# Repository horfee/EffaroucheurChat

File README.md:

# Effaroucheur à Chat

This project is a design of a board, based on ESP32, to control ultra sound speaker according to infrared motion sensors.

It is powered by 2 solar panels, with a LDO MP2161GJ-Z to power efficiently the device.

Used components are :
- MP2161GJ-Z
- ESP32 WROOM
- TP4056 as battery charger
- HC-SR501 for motion sensors
- << insert speaker ref here >>
- FT232RL to discuss with ESP32 for flash phase
- UMH3N to enabled RTS/DTR mechanism

Flash firmware will come later.

Current design is this :

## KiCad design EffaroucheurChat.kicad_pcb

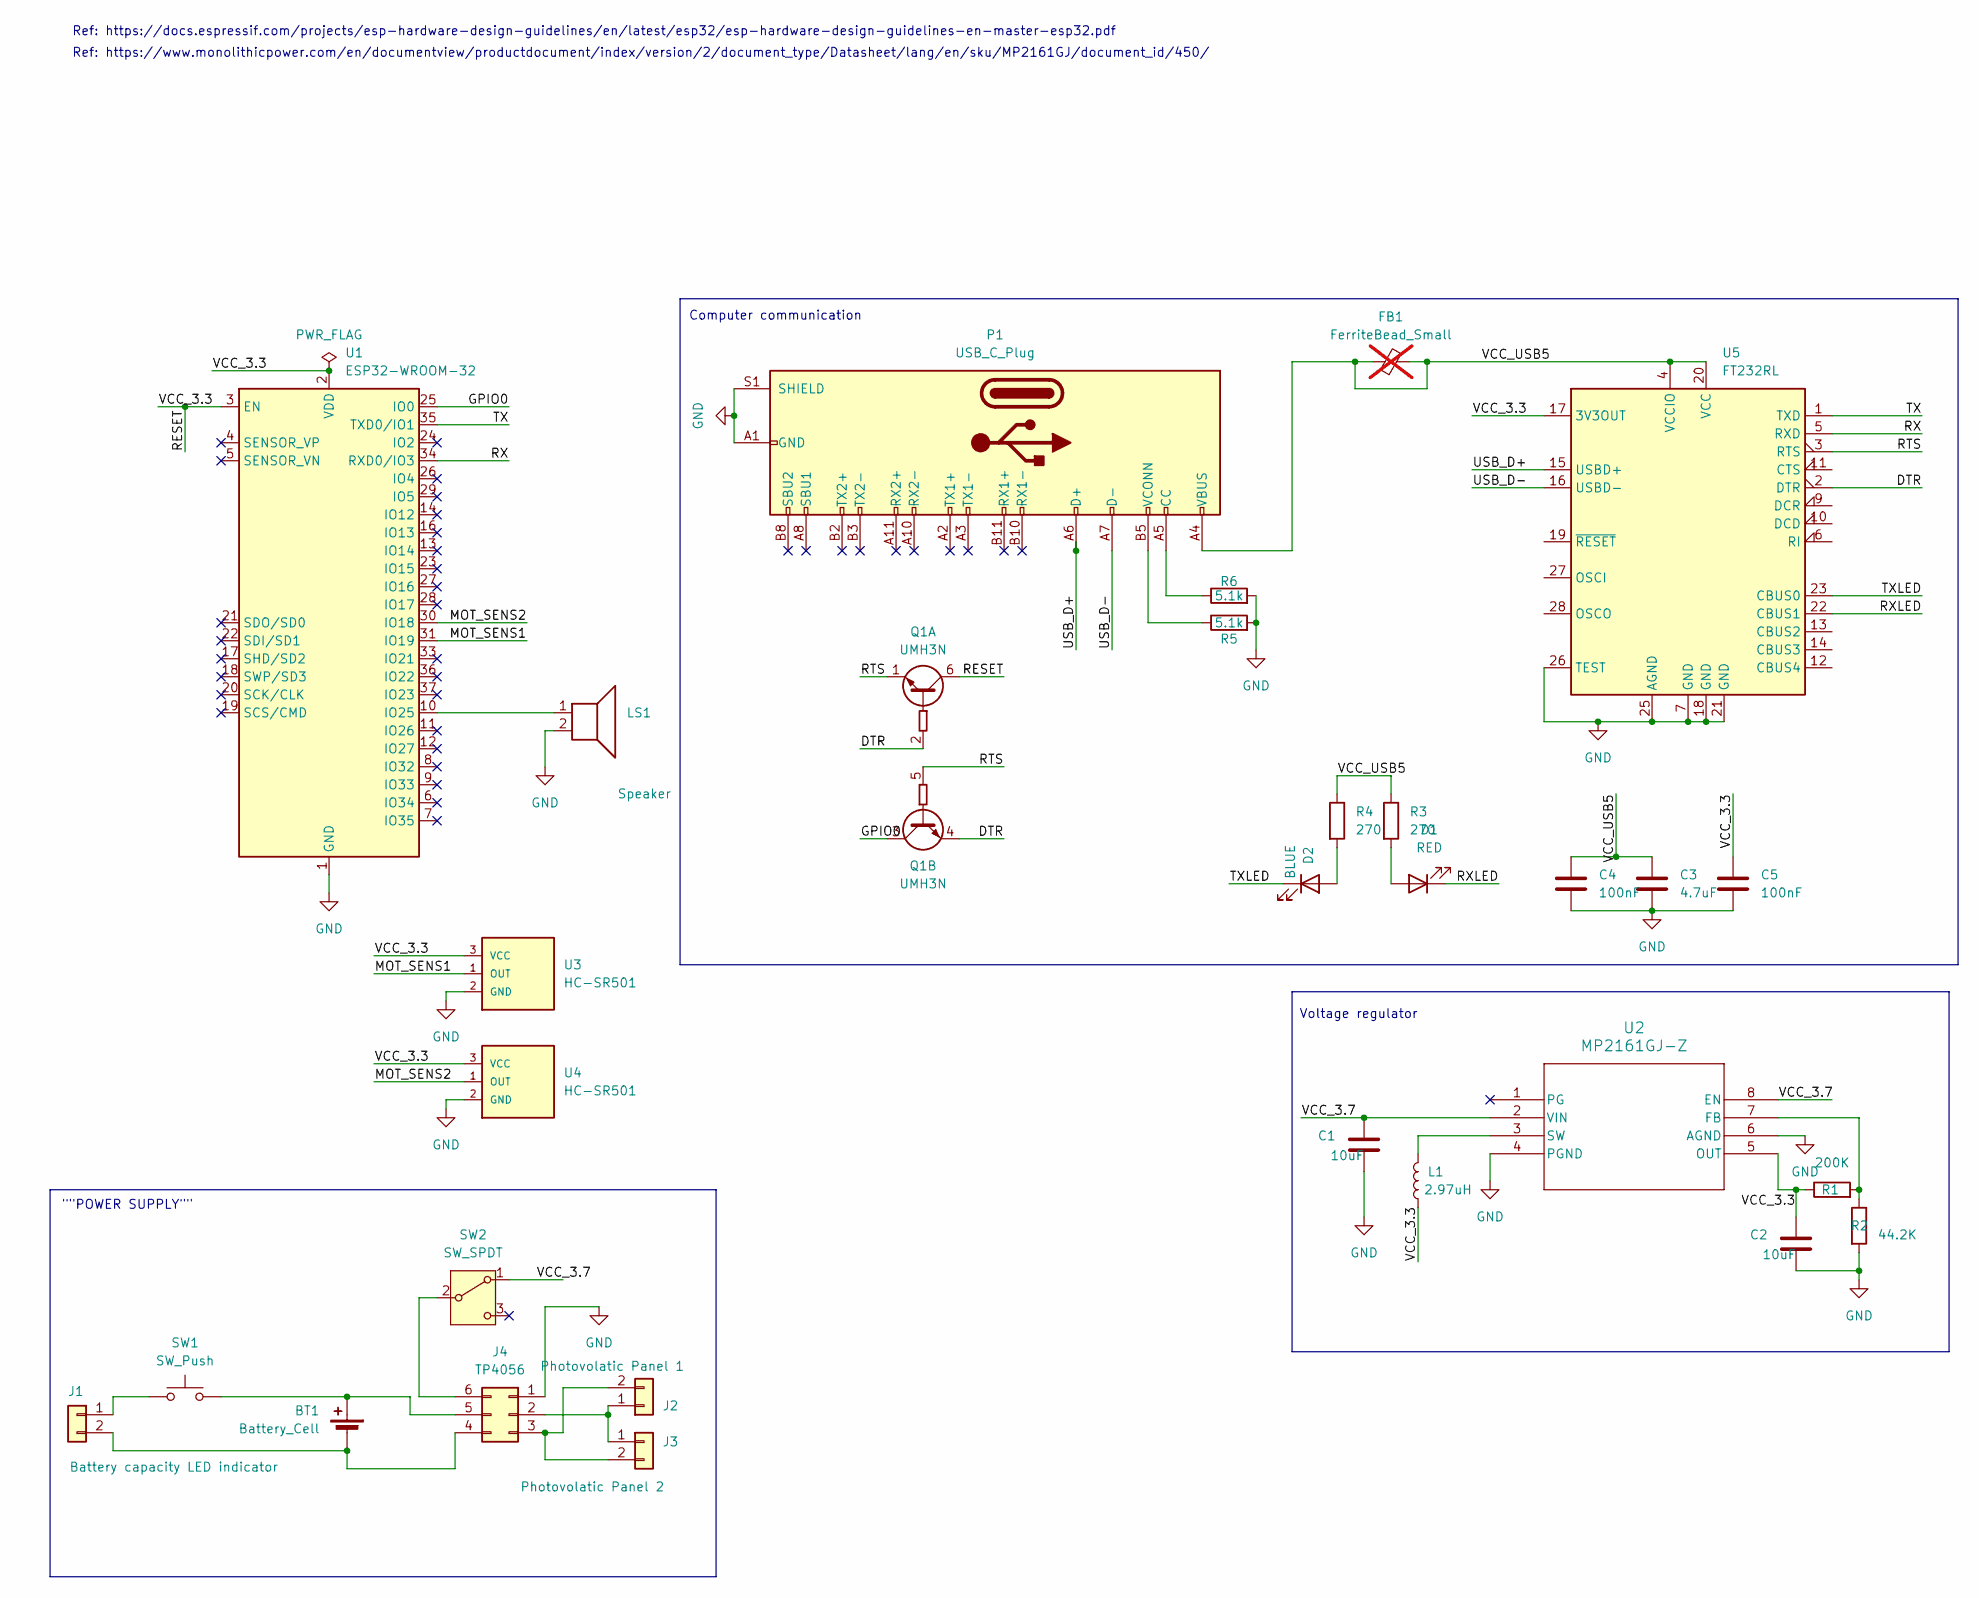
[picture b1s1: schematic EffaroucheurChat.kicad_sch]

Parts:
BT1: Battery_Cell
C1, C2: 10uF; C_3640_9110Metric
C3: 4.7uF; C_0805_2012Metric
C4, C5: 100nF; C_0805_2012Metric
D1: RED; LED_0805_2012Metric
D2: BLUE; LED_0805_2012Metric
FB1: FerriteBead_Small; not fitted
J1: Battery capacity LED indicator; PinHeader_1x02_P2.54mm_Vertical
J2: Photovolatic Panel 1; PinHeader_1x02_P2.54mm_Vertical
J3: Photovolatic Panel 2; PinHeader_1x02_P2.54mm_Vertical
J4: TP4056
L1: 2.97uH; L_0603_1608Metric_Pad1.05x0.95mm_HandSolder
LS1: Speaker; PinHeader_1x02_P2.54mm_Vertical
P1: USB_C_Plug; USB_C_Receptacle_GCT_USB4085
Q1: UMH3N; SOT-363_SC-70-6
R1: 200K; R_0805_2012Metric
R2: 44.2K; R_0805_2012Metric
R3, R4: 270; R_0805_2012Metric
R5, R6: 5.1k; R_0805_2012Metric
SW1: SW_Push; SW_Push_1P1T_NO_6x6mm_H9.5mm
SW2: SW_SPDT; PinHeader_1x02_P2.54mm_Vertical
U1: ESP32-WROOM-32
U2: MP2161GJ-Z; SOT-23-8_Handsoldering
U3, U4: HC-SR501; PinHeader_1x03_P2.54mm_Vertical
U5: FT232RL; SSOP-28_5.3x10.2mm_P0.65mm

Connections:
/DTR: Q1.2 (B1), Q1.4 (E2), U5.2 (DTR)
/GPIO0: Q1.3 (C2), U1.25 (IO0)
/MOT_SENS1: U1.31 (IO19), U3.1 (OUT)
/MOT_SENS2: U1.30 (IO18), U4.1 (OUT)
/RESET: C2.1, C5.1, L1.1, Q1.6 (C1), R1.1, U1.2 (VDD), U1.3 (EN), U2.5 (OUT), U3.3 (VCC), U4.3 (VCC), U5.17 (3V3OUT)
/RTS: Q1.1 (E1), Q1.5 (B2), U5.3 (RTS)
/RX: U1.34 (RXD0/IO3), U5.5 (RXD)
/RXLED: D1.1 (K), U5.22 (CBUS1)
/TX: U1.35 (TXD0/IO1), U5.1 (TXD)
/TXLED: D2.1 (K), U5.23 (CBUS0)
/USB_D+: P1.A6 (D+), U5.15 (USBD+)
/USB_D-: P1.A7 (D-), U5.16 (USBD-)
/VCC_3.7: C1.1, SW2.1 (A), U2.2 (VIN), U2.8 (EN)
/VCC_USB5: C3.1, C4.1, FB1.1, FB1.2, P1.A4 (VBUS), P1.A9 (VBUS), P1.B4 (VBUS), P1.B9 (VBUS), R3.1, R4.1, U5.4 (VCCIO), U5.20 (VCC)
GND: C1.2, C2.2, C3.2, C4.2, C5.2, J4.1, LS1.2, P1.A1 (GND), P1.A12 (GND), P1.B1 (GND), P1.B12 (GND), P1.S1 (SHIELD), R2.2, R5.2, R6.2, U1.1 (GND), U1.15 (GND), U1.38 (GND), U1.39 (GND), U2.4 (PGND), U2.6 (AGND), U3.2 (GND), U4.2 (GND), U5.7 (GND), U5.18 (GND), U5.21 (GND), U5.25 (AGND), U5.26 (TEST)
unnamed: BT1.1 (+), J4.5, SW1.2
unnamed: BT1.2 (-), J1.2, J4.4
unnamed: D1.2 (A), R3.2
unnamed: D2.2 (A), R4.2
unnamed: J1.1, SW1.1
unnamed: J2.1, J3.1, J4.2
unnamed: J2.2, J3.2, J4.3
unnamed: J4.6, SW2.2 (B)
unnamed: P1.A5 (CC), R6.1
unnamed: P1.B5 (VCONN), R5.1
unnamed: LS1.1, U1.10 (IO25)
unnamed: R1.2, R2.1, U2.7 (FB)
unnamed: L1.2, U2.3 (SW)

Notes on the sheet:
Computer communication
""POWER SUPPLY""
Voltage regulator
Ref: https://docs.espressif.com/projects/esp-hardware-design-guidelines/en/latest/esp32/esp-hardware-design-guidelines-en-master-esp32.pdf
Ref: https://www.monolithicpower.com/en/documentview/productdocument/index/version/2/document_type/Datasheet/lang/en/sku/MP2161GJ/document_id/450/

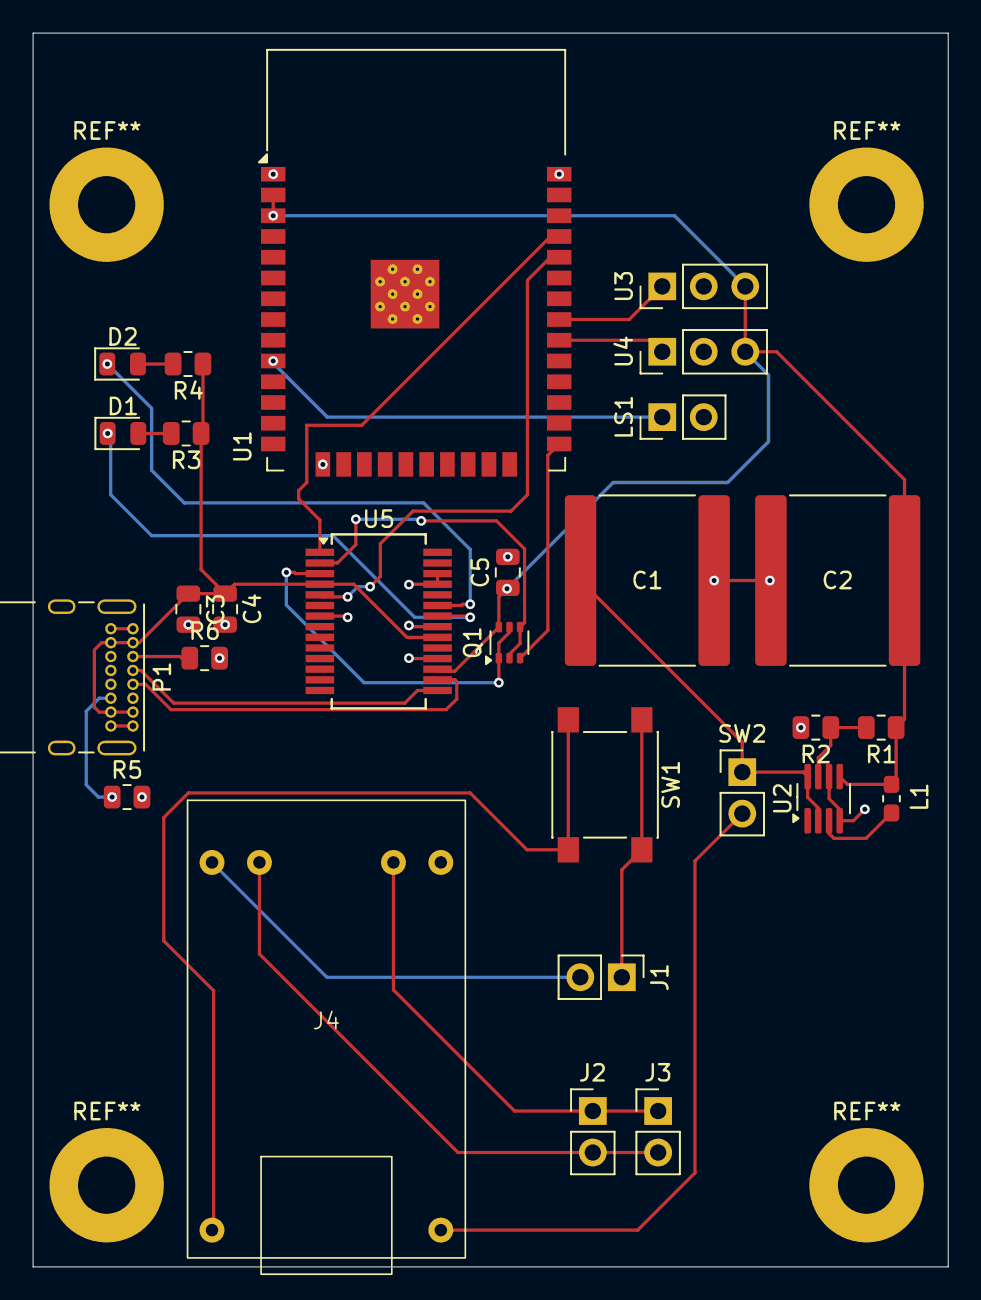
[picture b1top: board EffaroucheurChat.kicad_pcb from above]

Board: 4 copper layers, 56.0 x 75.5 mm, 28 parts (0 on the bottom side), 28 nets.
